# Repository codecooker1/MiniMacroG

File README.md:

MiniMicroG is a cute little macropad made following the [HackPad](https://blueprint.hackclub.com/starter-projects/hackpad) starter guide in Blueprint.

Used Components:
- Seeed XIAO RP2040 (x1)
- Through-hole 1N4148 Diodes (x6)
- MX-Style Switch (x6)
- EC11 Rotary Encoder (x1)
- 0.91 inch OLED display (x1)
- SK6812 MINI-E LED (x6)
- Blank DSA keycaps (x6)
- M3x16mm screws (x4)
- M3x5mx4mm heatset inserts (x4)
- 3D Printed Case (x1)

Here's the picture of the 3d render of PCB

Casing

If you are interested you can signup using my [referral link](https://blueprint.hackclub.com/r/1816?ref=r).

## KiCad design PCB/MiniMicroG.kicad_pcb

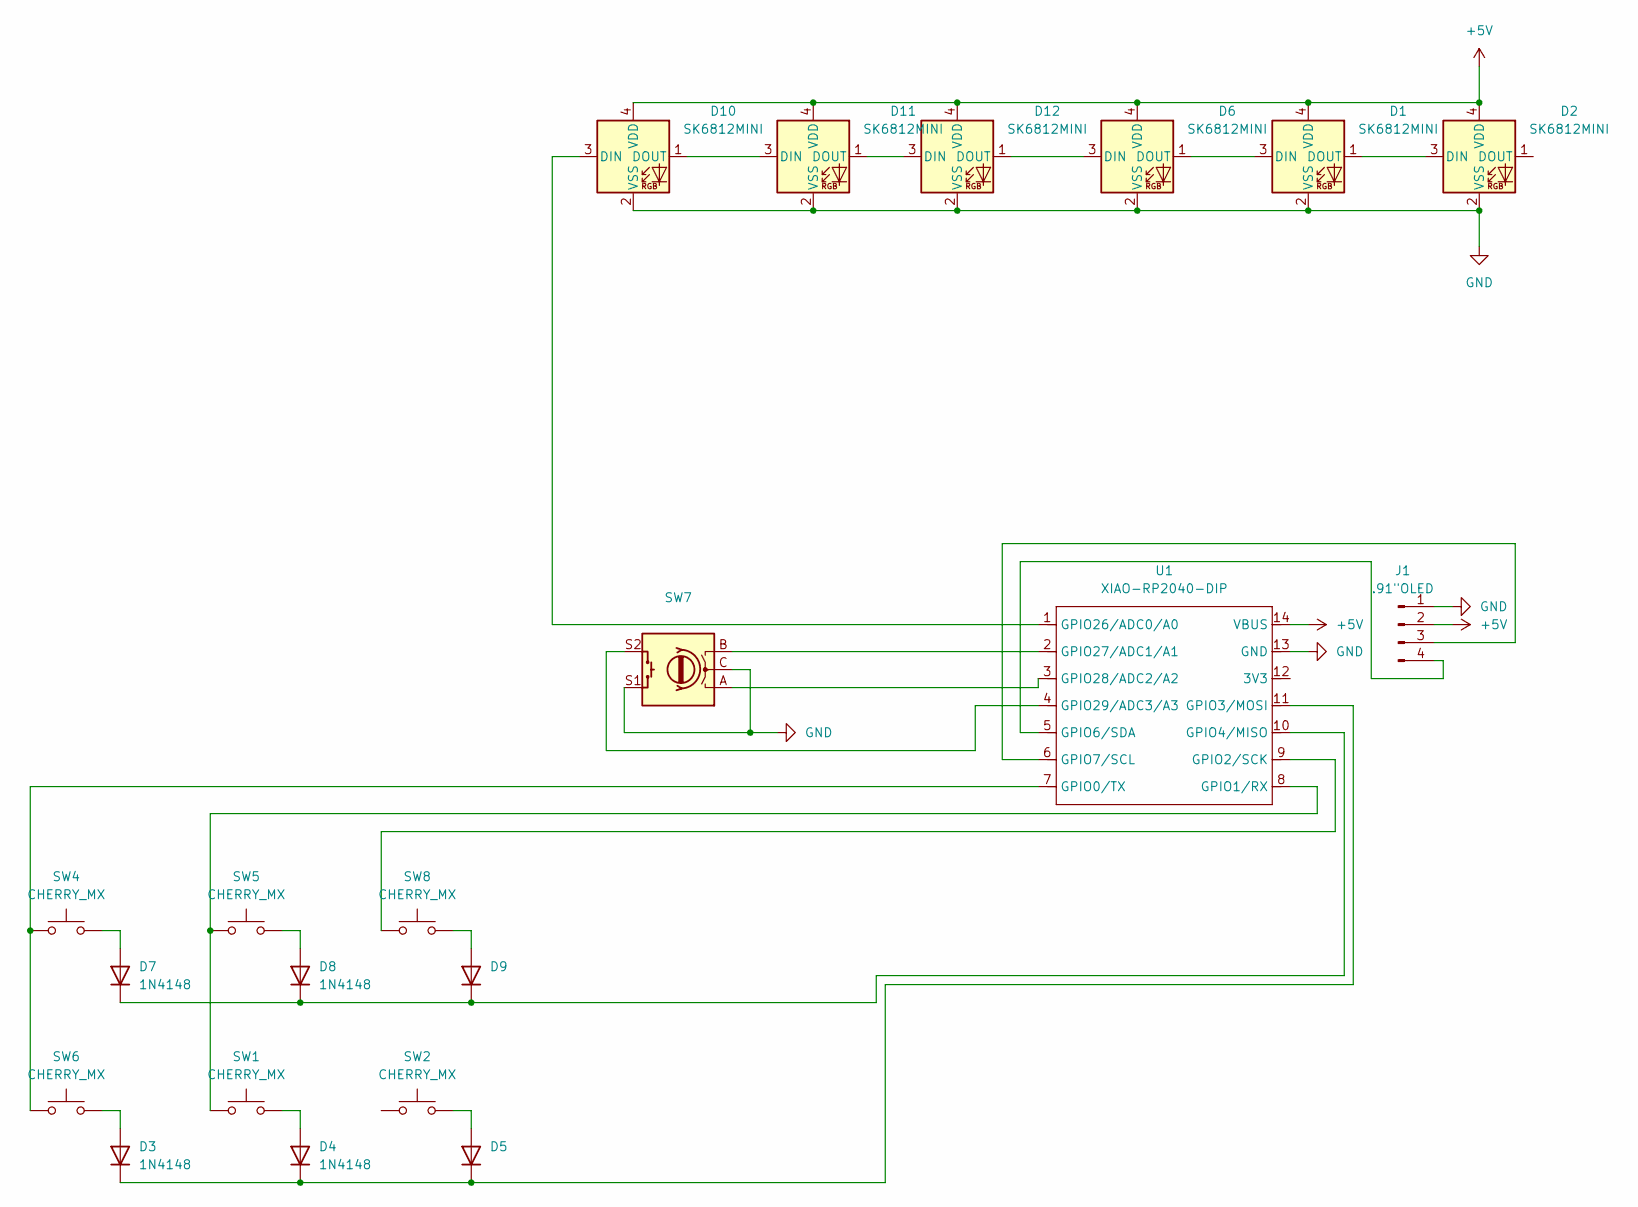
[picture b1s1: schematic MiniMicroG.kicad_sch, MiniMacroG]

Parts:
D1, D2, D6, D10, D11, D12: SK6812MINI; LED_SK6812MINI_PLCC4_3.5x3.5mm_P1.75mm
D3, D4, D5, D7, D8, D9: 1N4148; D_DO-35_SOD27_P7.62mm_Horizontal
J1: .91"OLED; SSD1306-0.91-OLED-4pin-128x32
SW1, SW2, SW4, SW5, SW6, SW8: CHERRY_MX; SW_Cherry_MX_1.00u_PCB
SW7: RotaryEncoder_Switch; RotaryEncoder_Alps_EC11E-Switch_Vertical_H20mm
U1: XIAO-RP2040-DIP

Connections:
+5V: D1.4 (VDD), D2.4 (VDD), D6.4 (VDD), D10.4 (VDD), D11.4 (VDD), D12.4 (VDD), J1.2, U1.14 (VBUS)
GND: D1.2 (VSS), D2.2 (VSS), D6.2 (VSS), D10.2 (VSS), D11.2 (VSS), D12.2 (VSS), J1.1, SW7.C, SW7.S1, U1.13 (GND)
unnamed: D1.3 (DIN), D6.1 (DOUT)
unnamed: D1.1 (DOUT), D2.3 (DIN)
unnamed: D3.2 (A), SW6.2
unnamed: D3.1 (K), D4.1 (K), D5.1 (K), U1.11 (GPIO3/MOSI)
unnamed: D4.2 (A), SW1.2
unnamed: D5.2 (A), SW2.2
unnamed: D7.2 (A), SW4.2
unnamed: D7.1 (K), D8.1 (K), D9.1 (K), U1.10 (GPIO4/MISO)
unnamed: D8.2 (A), SW5.2
unnamed: D9.2 (A), SW8.2
unnamed: D10.3 (DIN), U1.1 (GPIO26/ADC0/A0)
unnamed: D10.1 (DOUT), D11.3 (DIN)
unnamed: D11.1 (DOUT), D12.3 (DIN)
unnamed: D6.3 (DIN), D12.1 (DOUT)
unnamed: J1.3, U1.6 (GPIO7/SCL)
unnamed: J1.4, U1.5 (GPIO6/SDA)
unnamed: SW4.1, SW6.1, U1.7 (GPIO0/TX)
unnamed: SW1.1, SW5.1, U1.8 (GPIO1/RX)
unnamed: SW8.1, U1.9 (GPIO2/SCK)
unnamed: SW7.B, U1.2 (GPIO27/ADC1/A1)
unnamed: SW7.A, U1.3 (GPIO28/ADC2/A2)
unnamed: SW7.S2, U1.4 (GPIO29/ADC3/A3)

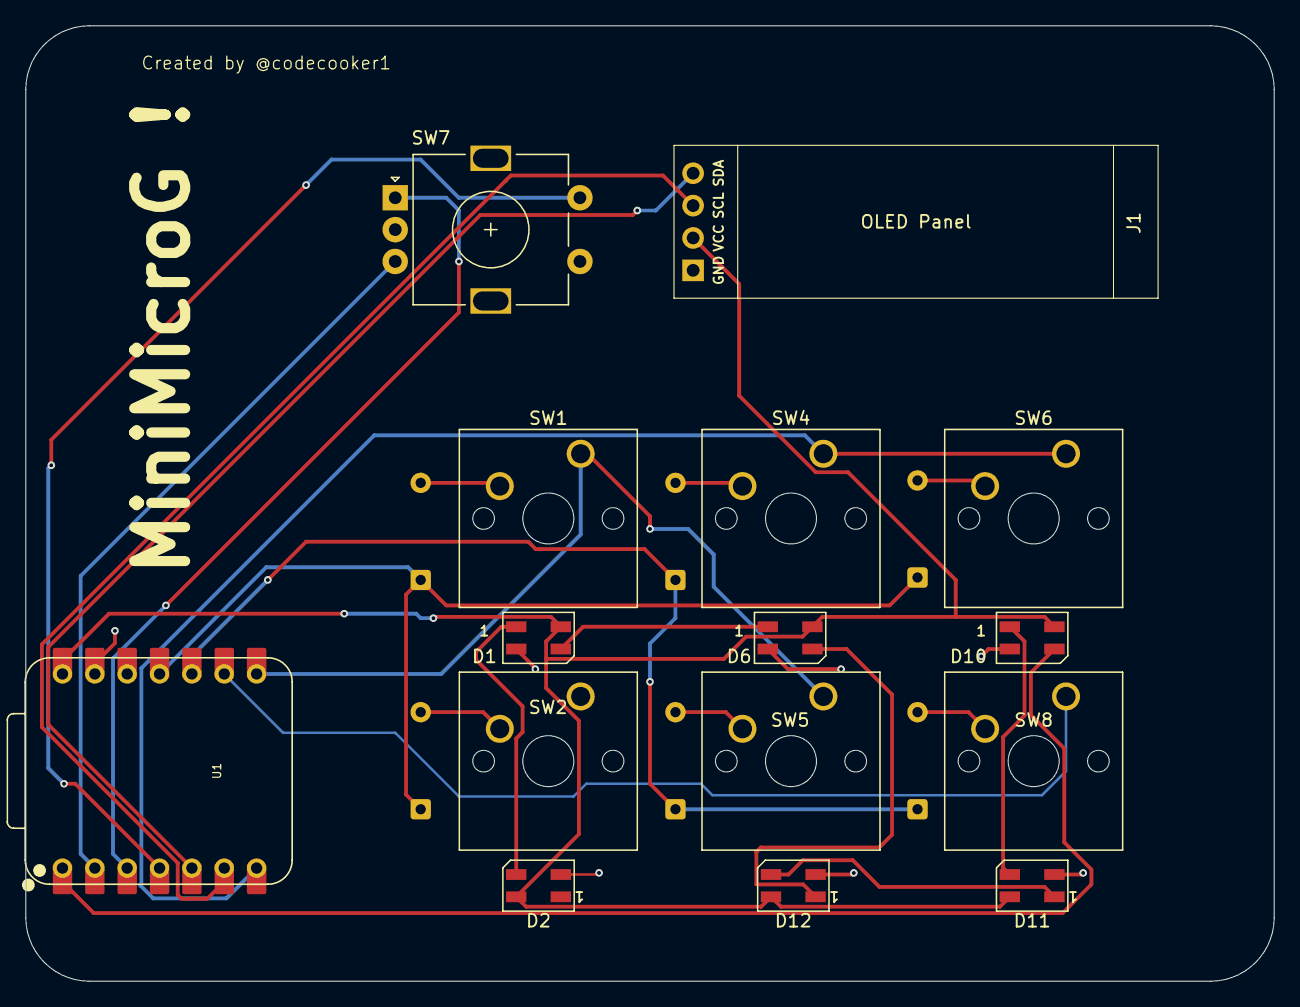
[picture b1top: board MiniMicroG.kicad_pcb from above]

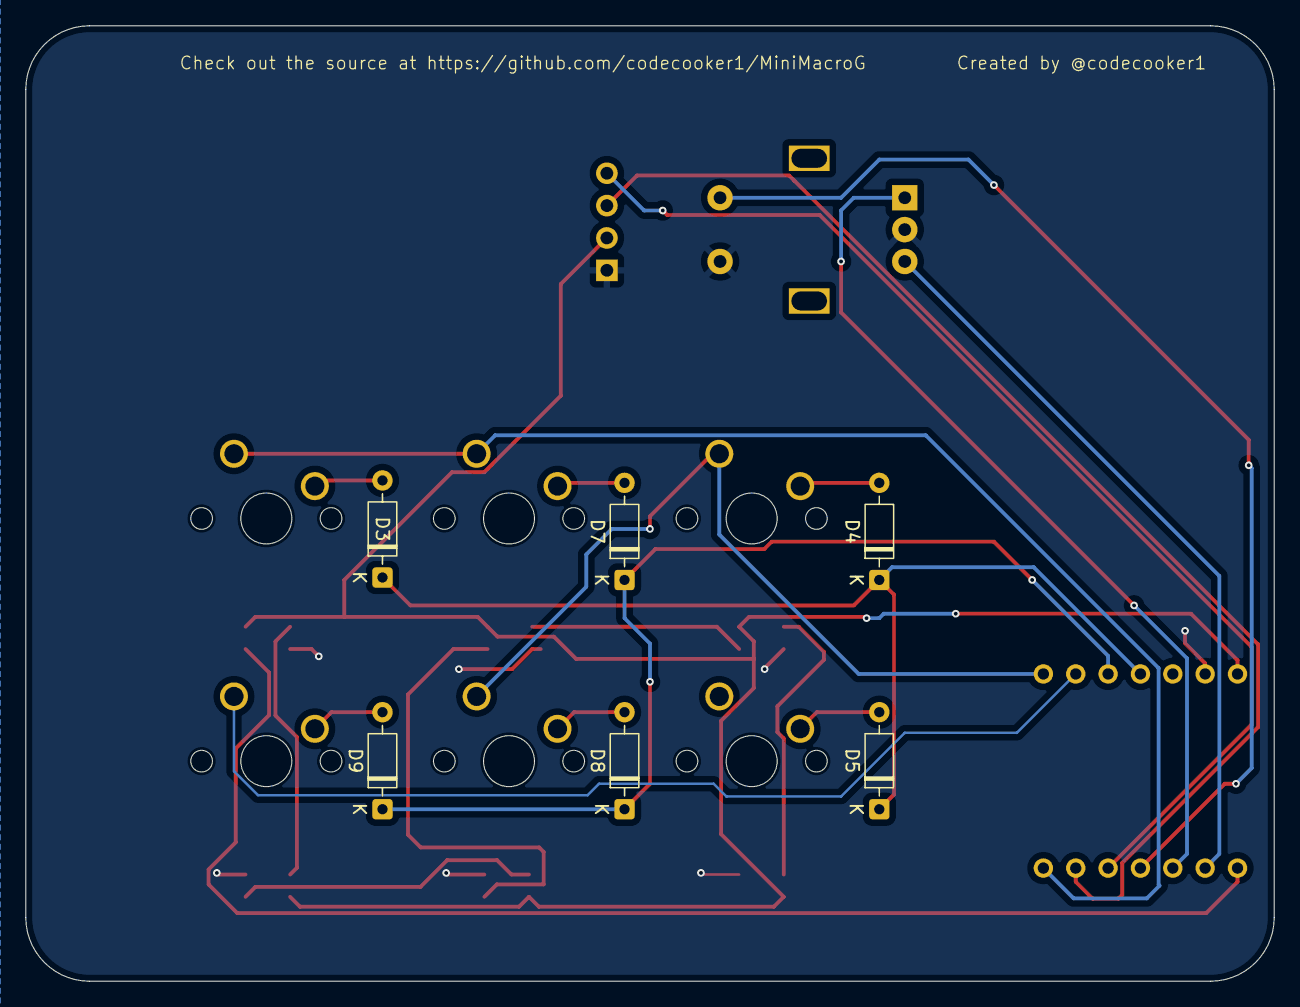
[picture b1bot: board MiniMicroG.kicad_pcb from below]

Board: 2 copper layers, 98.0 x 75.0 mm, 21 parts (6 on the bottom side), 24 nets.

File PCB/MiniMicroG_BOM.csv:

Id;Designator;Footprint;Quantity;Designation;Supplier and ref;Unit Price;Total Price;Link
1;SW7;RotaryEncoder_Alps_EC11E-Switch_Vertical_H20mm;1;RotaryEncoder_Switch;;;;
2;D2,D12,D11,D10,D6,D1;LED_SK6812MINI_PLCC4_3.5x3.5mm_P1.75mm;6;SK6812MINI;;;;
3;SW5,SW1,SW2,SW4,SW8,SW6;SW_Cherry_MX_1.00u_PCB;6;CHERRY_MX;;;;
4;U1;XIAO-RP2040-DIP;1;XIAO-RP2040-DIP;;;;
5;J1;SSD1306-0.91-OLED-4pin-128x32;1;".91""OLED";;;;
6;D9,D5,D7,D8,D4,D3;D_DO-35_SOD27_P7.62mm_Horizontal;6;1N4148;;;;

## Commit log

2025-11-14 Include PCB 3D render image in README
    Added a 3D render image of the PCB to the README.
2025-11-14 Revise journal entries for project progress
    Updated journal entries for Day 2 and Day 3.
2025-11-14 Succesfully Restructured
2025-11-14 bull
2025-11-14 create keyboard layout
2025-11-14 fix README
2025-11-16 Add 3D Models
2025-11-16 Update PCB
2025-11-17 Made the Casing
2025-11-17 Revise components list and add images
    Updated the components list with quantities and added images.
2025-12-09 Add GNU GPL v3 license
    Added the GNU General Public License version 3 to the project.
